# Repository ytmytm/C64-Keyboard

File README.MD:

# C128 version

I have forked this version from https://github.com/Hartland/C64-Keyboard for two reasons:

- design PCB to connect PS/2 keyboard with MT8808 and Arduino Micro Pro solution to C128D, directly to the keyboard port
- provide symbolic, rather than positional, mapping for the keys

Everything you need for this version is in PS2/C128_keyboard_MT8808 folder.

I have cleaned up the code and added named key value definitions to the [keymap file](PS2/C128_keyboard_MT8808/Firmware/keymapping.h) for easier mapping.

Have fun!

-- Maciej 'YTM/Elysium' Witkowiak

## Project cloning

This project uses external submodule with Arduino Micro Pro symbol and footprint.

Clone it with all submodules using:

```sh
git clone --recurse-submodules https://github.com/ytmytm/C64-Keyboard.git
```

## PCB and schematic

Use KiCad to open the project in PS2/C128_keyboard_MT8808/PCB folder.

Ready for use Gerber files for circuit board v1.0 are in PS2/C128_keyboard_MT8808/PCB/gerber folder.

## Firmware

Use Arduino IDE to compile and flash the code from PS2/C128_keyboard_MT8808/Firmware folder.

## C128 PS/2 version circuit assembly

Parts:

* 26-wire flat ribbon cable
* 26-pin ribbon cable connectors (male for PCB, female for crimping on the cable)
* DE25 male crimp connector for ribbon cable
* MT8808
* Arduino Micro Pro
* (optional) PS/2 socket
* (optional) 28-pin and 24-pin sockets

Assembly:

* align red (first) wire with triangular mark on the female connector and crimp it
* separate 26th wire and remove it from the cable, cut it off as close as possible to the already crimped connector
* now the cable can be aligned and crimped in the DE25 connector; aligh red (first) wire with the mark on connector, confirm that it goes to pin 1
* solder parts on the PCB, start with lowest profile components first (sockets, MT8808, male 26-pin connector)

You can skip over transistor and resistor and connect pin 3 from the cable directly to Arduino pin 16 using a jumper.
This part would be required on C64, but C128 has separate circuitry for RESTORE key, it's not tied directly to /NMI line.

Add two wire connections that I forgot to put on PCB in version 1:

* pin 24 to A0 (40/80 key)
* pin 25 to A1 (CAPS key)

## Keyboard mapping

| C64/128 key | PS/2 key |
|-------------|----------|
| C=		  | Windows  |
| RUN/STOP    | ESC, END, left ALT |
| RESTORE     | TAB |
| ARROW LEFT  | ` (tilde) |
| ARROW UP    | ^ (SHIFT+6) |
| @           | @ (SHIFT+2) |
| DEL         | DEL, BACKSPACE |
| CLR/HOME    | HOME |
| *           | * (SHIFT+8) |
| POUND       | \ |

## Function keys

| PS/2 key | action |
|----------|--------|
| F9       | symbolic keymap (default) |
| F10      | positional keymap |
| F11      | C128 CAPS toggle |
| F12      | C128 40/80 toggle |
| CAPS LOCK | SHIFT LOCK toggle |
| SysRq    | reset MT8808 |

## BUGS

Left (right too?) SHIFT release must be *after* shifted key release. Otherwise the shifted key is stuck until exact the same sequence is entered again.
It's quite annoying for '@' and ':'.

## TODOs

To do in PCB version 2:

* connect C128 40/80 line (pin 24) to A0
* connect C128 CAPS line (pin 25) to A1
* connect RESTORE line (pin 3) directly to pin 16, no need for transistor and resistor there (true for 5V Arduino, certainly not for SEEDUINO)
* correct parts alignment so that mounting holes are not obscured
* use PS/2 socket footprint
* use DB25 male socket footprint for direct connection
* use 1x25 footprint for C64 compatibility
* +5V jumper between Arduino VCC and +5V net (serial port, PS/2 port and DE25 pin 4)

To do for MT8812/MT8816 version:

* handle extra C128 keys using DE25 pins 21/22/23 (K0/K1/K2)

To do for SEEDUINO version:

* there is not enough pins, I/O expander or latch is needed, 74'595 is enough for this
* 3x transistor + 3x 10K resistor for /RESTORE, 40/80 and CAPS required

# Original documentation follows

## C64 PS2/USB Keyboard

This project is designed to allow a PS2/USB keyboard to be used with a Commodore 64 in place of the original Commodore keyboard.

Dependencies
------------
* PS2KeyAdvanced Arduino library for use with PS2 keyboard. Install through the IDE library manager

* SEEED XIAO uses slightly modified USBHOST Arduino library (C64_USB_Host_Library_SAMD). This directory will need to be copied into the Arduino library directory.

* SEEED XIAO will need its board driver installed into the Arduino IDE. See manufacturers instructions.

* DUE also uses a modified USBHOST library but it is included with the source and does not need to be installed in the library directory.

Hardware
--------
* Arduino Uno, Nano, DUE, or SEEED XIAO. SEEED XIAO or DUE required for USB keyboard

* MT8808, MT8812 or MT8816 Analog Switch Array

* 20 pin female header or male header with cable (PATA cable will work)

* Arduino shield PCB. 
	- Any universal PCB that will line up correctly

* PS2 keyboard 
	- matching socket or cut/strip and directly wire
	
* USB keyboard - **SEEED XIAO is highly recommended as the DUE is overkill for this project** 
	- Requires SEEED XIAO or DUE. In most cases, the SEED requires USB Type C to USB A or Micro Type B cable/adapter
	- Keyboards that connect through internal USB hubs are not supported.This is a limitation of the USBHost library
	- Restore (NMI) key requires a NPN transistor (2n3904 suggested) and resistor (10K)

Documents
---------

* KEYBIN.PDF
	- MT88XX AY/AX. These are the hard wired Commodore keyboard header position values used in keyboard mapping.
	- The position values are placed on the keymap where the PS2/USB keyboard value matches the Commodore key desired.
	- The AX2-1-0 AY2-1-0 and logic hole hole columns are for reference and not needed to make keymaps. 
	- The logic hole column only applies to the MT8812-16.
	
* DEFAULTKEY.TXT
	- Key map of special function keys (EX. C= key mapped to Windows key)
	
* USB_KEY_CODES.TXT
	- Public Domain copy of USB HID scan codes.
	
* Schematic PDF files
	- Include wiring charts and are located in the PS2 and USB folders under the appropriate board type
	- MT8808 and MT8812-16 are separate due to a different MT88xx pinouts 

Usage
-----

* PS2 keyboards use the PS2KeyAdvanced library.
	-Use Manage Library to search for and install PS2KeyAdvanced.

* USB Keyboards use the included modified USBHOST.

* Using the Arduino IDE upload the sketch: *C64_keyboard.ino* into your Arduino.

* **SYSTEM OPTIONS ARE LOCATED IN THE *C64KEYBOARD.H* HEADER FILE. THE MT8808 DEFINITION IS VERY IMPORTANT. SET TO TRUE IF USING A MT8808 OR FALSE IF USING MT8812-16.**

!!!POWER REQUIREMENTS!!!!
-------------------------

* The Arduino UNO, Nano, and SEEED can be powered from the C64 keyboard header Pin 4

* **The Arduino DUE CANNOT BE POWERED FROM PIN 4!! Use the + side of C10 (+10V) connected to the DUE barrel power connector instead.**

TODO
----

* Create spreadsheet/program to automatically create key maps

* Publish pre-compiled binary files

Version 1.00
-------------
* Updated and cleaned up all schematics and documents. All wiring charts are now on the schematics.

* DUE has been brought out of archive status and will be part of future updates.

Version 0.920
-------------
* Add SEEED XIAO board for USB keyboards

* Document DUE is for archive only

Version 0.911
-------------
* USB IDE library requirement removed

Version 0.91
------------
* USB module published

Version 0.9
------------
* Code rewrite using PS2KeyAdvanced library

* Several bugs have been fixed

* Speed and reliability have been greatly improved

* Up to 2 key maps can be stored and hot swapped with assigned keys (Default F9-F10)

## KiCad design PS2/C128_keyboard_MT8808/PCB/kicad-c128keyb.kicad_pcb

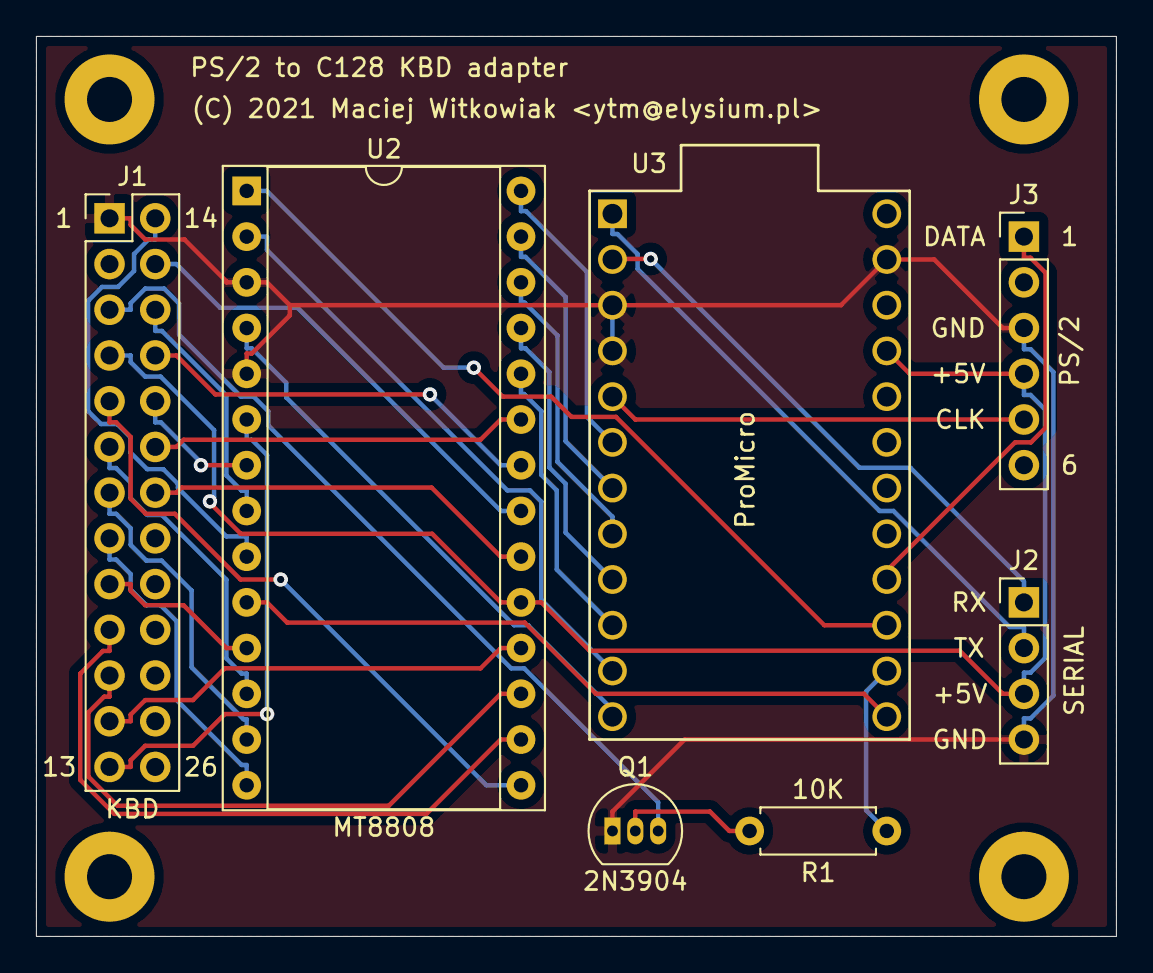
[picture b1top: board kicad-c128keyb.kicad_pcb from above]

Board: 2 copper layers, 60.0 x 50.0 mm, 7 parts (0 on the bottom side), 34 nets.

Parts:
J1: KBD; Pin_Header_Straight_2x13_Pitch2.54mm
J2: SERIAL; Pin_Header_Straight_1x04_Pitch2.54mm
J3: Mini-DIN-6; Pin_Header_Straight_1x06_Pitch2.54mm
Q1: 2N3904; TO-92_Inline_Narrow_Oval
R1: 10K; R_Axial_DIN0207_L6.3mm_D2.5mm_P7.62mm_Horizontal
U2: MT8808; DIP-28_W15.24mm_Socket
U3: ProMicro

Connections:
/PS2CLK: J3.5, U3.5
/PS2DATA: J3.1, U3.16
/RX: J2.1, U3.2
/TX: J2.2, U3.1
/~NMI: J1.3, Q1.3
GND: J1.1, J2.4, J3.3, Q1.1, U2.3, U2.5, U3.3, U3.4, U3.23
unnamed: J1.5, U2.15
unnamed: J1.6, U2.12
unnamed: J1.7, U2.13
unnamed: J1.8, U2.14
unnamed: J1.9, U2.11
unnamed: J1.10, U2.16
unnamed: J1.11, U2.17
unnamed: J1.12, U2.18
unnamed: J1.13, U2.6
unnamed: J1.14, U2.9
unnamed: J1.15, U2.21
unnamed: J1.16, U2.8
unnamed: J1.17, U2.22
unnamed: J1.18, U2.7
unnamed: J1.19, U2.23
unnamed: J1.20, U2.20
unnamed: Q1.2, R1.2
unnamed: R1.1, U3.14
unnamed: U2.1, U3.15
unnamed: U2.2, U3.11
unnamed: U2.4, U3.12
unnamed: U2.10, U3.13
unnamed: U2.24, U3.10
unnamed: U2.25, U3.9
unnamed: U2.26, U3.8
unnamed: U2.27, U3.7
unnamed: U2.28, U3.6
VCC: J1.4, J2.3, J3.4, U2.19, U3.21

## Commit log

2021-11-11 import of untracked project files
2021-11-11 update docs about C128 version
2021-11-11 project photos
2021-11-11 rescaled
2021-11-11 typo
2022-05-25 updated docs
2022-05-25 sync with origin https://github.com/Hartland/C64-Keyboard
2022-05-25 more comments
2022-05-27 PCB project with FLAT26 and DB25 + SEEEDUINO XIAO

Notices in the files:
PS2/C128_keyboard_MT8808/PCB/kicad-c128keyb.kicad_pcb:
(C) 2021 Maciej Witkowiak
